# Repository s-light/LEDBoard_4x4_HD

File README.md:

<!--lint disable list-item-indent-->
<!--lint disable list-item-bullet-indent-->

# LEDBoard_4x4_HD
PCB originally designed for [magic_amulet](https://github.com/s-light/magic_amulet),  
but now used in [magic_crystal](https://github.com/s-light/magic_crystal)

Overall Size:  
33mm x 14mm

### PCB
4layer board - uses 150mil traces and 100mil trace spacing  
shown pcb came from [aisler](https://aisler.net/s-light/magic_amulet/led-board-4x4-hd)

### parts
LED-Driver: [TLC5957](http://www.ti.com/lit/ds/symlink/tlc5957.pdf) (48ch CC 9-16Bit-PWM driver)  
more information in AppNote [Build a High-Density, High-Refresh Rate, Multiplexing Panel With the TLC5957](http://www.ti.com/lit/ug/slvuaf0/slvuaf0.pdf)

LED: [Rohm MSL0402RGBU](https://www.rohm.com/products/led/chip-leds-multi-color-type/msl0402rgbu-product) (1.8x1.6x0.5mm RGB)

### BOM
can be ordered with aisler parts-package  
or also with this [list at mouser](https://www.mouser.com/ProjectManager/ProjectDetail.aspx?AccessID=e53c13ed09)  
or with plain part numbers:
```
Qty.    Mfr. No             Manufacturer            Description
16      MSL0402RGBU1        ROHM Semiconductor      Standard LEDs - SMD RGB 624/527/470nm 5V 400/550/180mcd 30mA
1       TLC5957RTQR         Texas Instruments       LED Lighting Drivers 48-channel, 16bit ES PWM LED driver
2       GRM188R61A226ME15D  Murata                  Multilayer Ceramic Capacitors MLCC - SMD/SMT 0603 22uF 10volts *Derate Voltage/Temp
2       GCM188R91E104KA37D  Murata                  Multilayer Ceramic Capacitors MLCC - SMD/SMT 0603 0.1uF 25volts X8R 10%
1       ERJ-PB3B7501V       Panasonic               Thick Film Resistors - SMD 0603 Anti-Surge Res. 0.1%, 7.5Kohm
```

### power & cooling
if you want to drive the leds with full power (up to 25mA/color)
you definitely need a heatsink.  
the pcb backside get to >= 60°C very fast without a heatsink!

also remember that one board needs up to 1.2A@5V = 6W

### constant current

```
RIREF(kΩ) = VIREF(V) / IOLCMax(mA)× Gain  | / Gain
RIREF(kΩ) / Gain = VIREF(V) / IOLCMax(mA)  | swap
Gain / RIREF(kΩ) = IOLCMax(mA) / VIREF(V)  | x VIREF(V)
Gain / RIREF(kΩ) x VIREF(V) = IOLCMax(mA)

Gain / 7.4kΩ x 1.2V = IOLCMax(mA)

```
|  Gain |  BC | IOLCMax |
| ----: | --: | ------: |
|  20.0 | 0x0 |   3.2mA |
|  39.5 | 0x1 |   6.4mA |
|  58.6 | 0x2 |   9.5mA |
|  80.9 | 0x3 |  13.1mA |
| 100.0 | 0x4 |  16.2mA |
| 113.3 | 0x5 |  18.4mA |
| 141.6 | 0x6 |  23.0mA |
| 154.5 | 0x7 |  25.0mA |

### Software
- [arduino library](https://github.com/s-light/slight_TLC5957)
- [CircuitPython library](https://github.com/s-light/slight_CircuitPython_TLC5957)

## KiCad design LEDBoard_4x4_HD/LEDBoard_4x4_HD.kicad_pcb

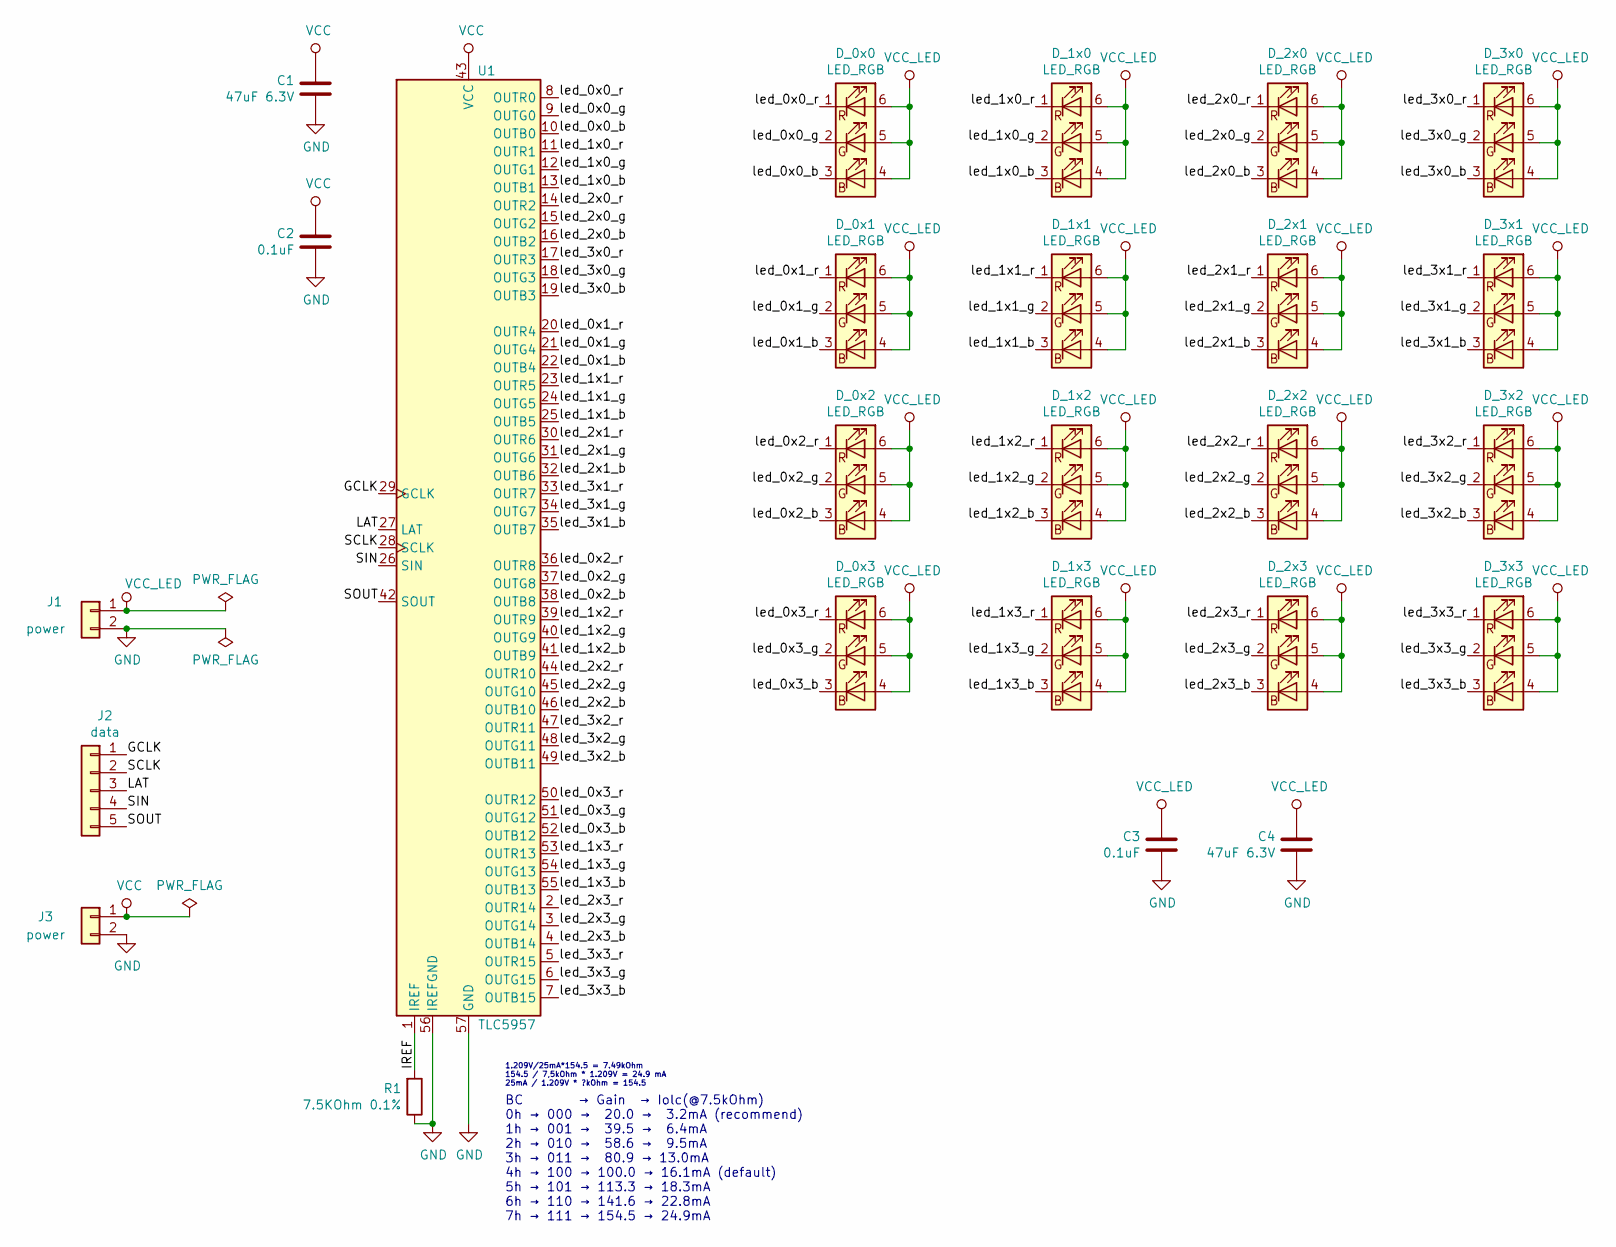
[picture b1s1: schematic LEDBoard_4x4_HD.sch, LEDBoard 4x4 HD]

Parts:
C1, C4: 47uF 6.3V; C_0603_1608Metric_Pad1.05x0.95mm_HandSolder
C2, C3: 0.1uF; C_0603_1608Metric_Pad1.05x0.95mm_HandSolder
D_0x0, D_0x1, D_0x2, D_0x3, D_1x0, D_1x1, D_1x2, D_1x3, D_2x0, D_2x1, D_2x2, D_2x3, D_3x0, D_3x1, D_3x2, D_3x3: LED_RGB; LED_RGB_0706_1816Metric_ROHM_ThermalVias
J1, J3: power; Conn_01x02_SMD_90deg_SolderMount
J2: data; Conn_01x05_SMD_90deg_SolderMount
R1: 7.5KOhm 0.1%; R_0603_1608Metric_Pad1.05x0.95mm_HandSolder
U1: TLC5957; QFN-56-1EP_8x8mm_P0.5mm_EP5.6x5.6mm_ThermalVias

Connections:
/GCLK: J2.1, U1.29 (GCLK)
/IREF: R1.2, U1.1 (IREF)
/LAT: J2.3, U1.27 (LAT)
/SCLK: J2.2, U1.28 (SCLK)
/SIN: J2.4, U1.26 (SIN)
/SOUT: J2.5, U1.42 (SOUT)
/led_0x0_b: D_0x0.3 (BK), U1.10 (OUTB0)
/led_0x0_g: D_0x0.2 (GK), U1.9 (OUTG0)
/led_0x0_r: D_0x0.1 (RK), U1.8 (OUTR0)
/led_0x1_b: D_0x1.3 (BK), U1.22 (OUTB4)
/led_0x1_g: D_0x1.2 (GK), U1.21 (OUTG4)
/led_0x1_r: D_0x1.1 (RK), U1.20 (OUTR4)
/led_0x2_b: D_0x2.3 (BK), U1.38 (OUTB8)
/led_0x2_g: D_0x2.2 (GK), U1.37 (OUTG8)
/led_0x2_r: D_0x2.1 (RK), U1.36 (OUTR8)
/led_0x3_b: D_0x3.3 (BK), U1.52 (OUTB12)
/led_0x3_g: D_0x3.2 (GK), U1.51 (OUTG12)
/led_0x3_r: D_0x3.1 (RK), U1.50 (OUTR12)
/led_1x0_b: D_1x0.3 (BK), U1.13 (OUTB1)
/led_1x0_g: D_1x0.2 (GK), U1.12 (OUTG1)
/led_1x0_r: D_1x0.1 (RK), U1.11 (OUTR1)
/led_1x1_b: D_1x1.3 (BK), U1.25 (OUTB5)
/led_1x1_g: D_1x1.2 (GK), U1.24 (OUTG5)
/led_1x1_r: D_1x1.1 (RK), U1.23 (OUTR5)
/led_1x2_b: D_1x2.3 (BK), U1.41 (OUTB9)
/led_1x2_g: D_1x2.2 (GK), U1.40 (OUTG9)
/led_1x2_r: D_1x2.1 (RK), U1.39 (OUTR9)
/led_1x3_b: D_1x3.3 (BK), U1.55 (OUTB13)
/led_1x3_g: D_1x3.2 (GK), U1.54 (OUTG13)
/led_1x3_r: D_1x3.1 (RK), U1.53 (OUTR13)
/led_2x0_b: D_2x0.3 (BK), U1.16 (OUTB2)
/led_2x0_g: D_2x0.2 (GK), U1.15 (OUTG2)
/led_2x0_r: D_2x0.1 (RK), U1.14 (OUTR2)
/led_2x1_b: D_2x1.3 (BK), U1.32 (OUTB6)
/led_2x1_g: D_2x1.2 (GK), U1.31 (OUTG6)
/led_2x1_r: D_2x1.1 (RK), U1.30 (OUTR6)
/led_2x2_b: D_2x2.3 (BK), U1.46 (OUTB10)
/led_2x2_g: D_2x2.2 (GK), U1.45 (OUTG10)
/led_2x2_r: D_2x2.1 (RK), U1.44 (OUTR10)
/led_2x3_b: D_2x3.3 (BK), U1.4 (OUTB14)
/led_2x3_g: D_2x3.2 (GK), U1.3 (OUTG14)
/led_2x3_r: D_2x3.1 (RK), U1.2 (OUTR14)
/led_3x0_b: D_3x0.3 (BK), U1.19 (OUTB3)
/led_3x0_g: D_3x0.2 (GK), U1.18 (OUTG3)
/led_3x0_r: D_3x0.1 (RK), U1.17 (OUTR3)
/led_3x1_b: D_3x1.3 (BK), U1.35 (OUTB7)
/led_3x1_g: D_3x1.2 (GK), U1.34 (OUTG7)
/led_3x1_r: D_3x1.1 (RK), U1.33 (OUTR7)
/led_3x2_b: D_3x2.3 (BK), U1.49 (OUTB11)
/led_3x2_g: D_3x2.2 (GK), U1.48 (OUTG11)
/led_3x2_r: D_3x2.1 (RK), U1.47 (OUTR11)
/led_3x3_b: D_3x3.3 (BK), U1.7 (OUTB15)
/led_3x3_g: D_3x3.2 (GK), U1.6 (OUTG15)
/led_3x3_r: D_3x3.1 (RK), U1.5 (OUTR15)
GND: C1.1, C2.1, C3.1, C4.1, J1.2, J3.2, R1.1, U1.56 (IREFGND), U1.57 (GND)
VCC: C1.2, C2.2, J3.1, U1.43 (VCC)
VCC_LED: C3.2, C4.2, D_0x0.4 (BA), D_0x0.5 (GA), D_0x0.6 (RA), D_0x1.4 (BA), D_0x1.5 (GA), D_0x1.6 (RA), D_0x2.4 (BA), D_0x2.5 (GA), D_0x2.6 (RA), D_0x3.4 (BA), D_0x3.5 (GA), D_0x3.6 (RA), D_1x0.4 (BA), D_1x0.5 (GA), D_1x0.6 (RA), D_1x1.4 (BA), D_1x1.5 (GA), D_1x1.6 (RA), D_1x2.4 (BA), D_1x2.5 (GA), D_1x2.6 (RA), D_1x3.4 (BA), D_1x3.5 (GA), D_1x3.6 (RA), D_2x0.4 (BA), D_2x0.5 (GA), D_2x0.6 (RA), D_2x1.4 (BA), D_2x1.5 (GA), D_2x1.6 (RA), D_2x2.4 (BA), D_2x2.5 (GA), D_2x2.6 (RA), D_2x3.4 (BA), D_2x3.5 (GA), D_2x3.6 (RA), D_3x0.4 (BA), D_3x0.5 (GA), D_3x0.6 (RA), D_3x1.4 (BA), D_3x1.5 (GA), D_3x1.6 (RA), D_3x2.4 (BA), D_3x2.5 (GA), D_3x2.6 (RA), D_3x3.4 (BA), D_3x3.5 (GA), D_3x3.6 (RA), J1.1

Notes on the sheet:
BC → Gain → Iolc(@7.5kOhm) 0h → 000 → 20.0 → 3.2mA (recommend) 1h → 001 → 39.5 → 6.4mA 2h → 010 → 58.6 → 9.5mA 3h → 011 → 80.9 → 13.0mA 4h → 100 → 100.0 → 16.1mA (default) 5h → 101 → 113.3 → 18.3mA 6h → 110 → 141.6 → 22.8mA 7h → 111 → 154.5 → 24.9mA
1.209V/25mA*154.5 = 7.49kOhm 154.5 / 7,5kOhm * 1.209V = 24.9 mA 25mA / 1.209V * ?kOhm = 154.5

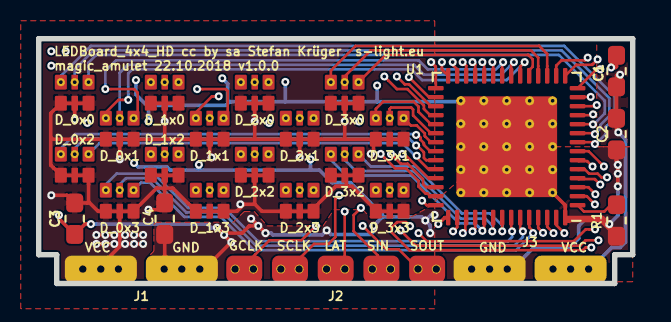
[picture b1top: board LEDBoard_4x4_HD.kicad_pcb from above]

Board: 4 copper layers, 33.0 x 13.6 mm, 25 parts (0 on the bottom side), 57 nets.

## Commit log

2018-10-16 added LEDBoard_4x4_HD
2018-10-19 fix gitignore
2018-10-19 clean up backups
2018-10-19 LEDBoard parts positioned & routing started
2018-10-20 first routing done
2018-10-20 first layout finished
2018-10-20 added dimensions & exported step
2018-10-21 updated pcb fixed some small things added capacitor
2018-10-22 more layout tweeks + separate VCC for controler
2018-10-22 some more clean up and exporting
2018-10-22 fixed silk print
2018-10-22 fixed zone connection for pad
2018-10-22 fixed position of connector labels
2018-10-22 added LED-models
2018-10-26 :memo: readme update
2018-10-26 :memo: added Links to LEDDriver
2018-10-26 :memo: more documentation
2018-10-26 :memo: updated TODO
2018-11-27 added pictures & updated readme
2019-03-09 rearranged folder structure
2019-03-09 [readme] fixed broken images
2019-03-09 [readme] update
2019-03-20 add power info
2019-03-24 updated component
2022-04-20 update readme + some older tweaks

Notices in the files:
LEDBoard_4x4_HD/LEDBoard_4x4_HD.kicad_pcb:
LEDBoard_4x4_HD cc by sa Stefan Krüger  s-light.eu
